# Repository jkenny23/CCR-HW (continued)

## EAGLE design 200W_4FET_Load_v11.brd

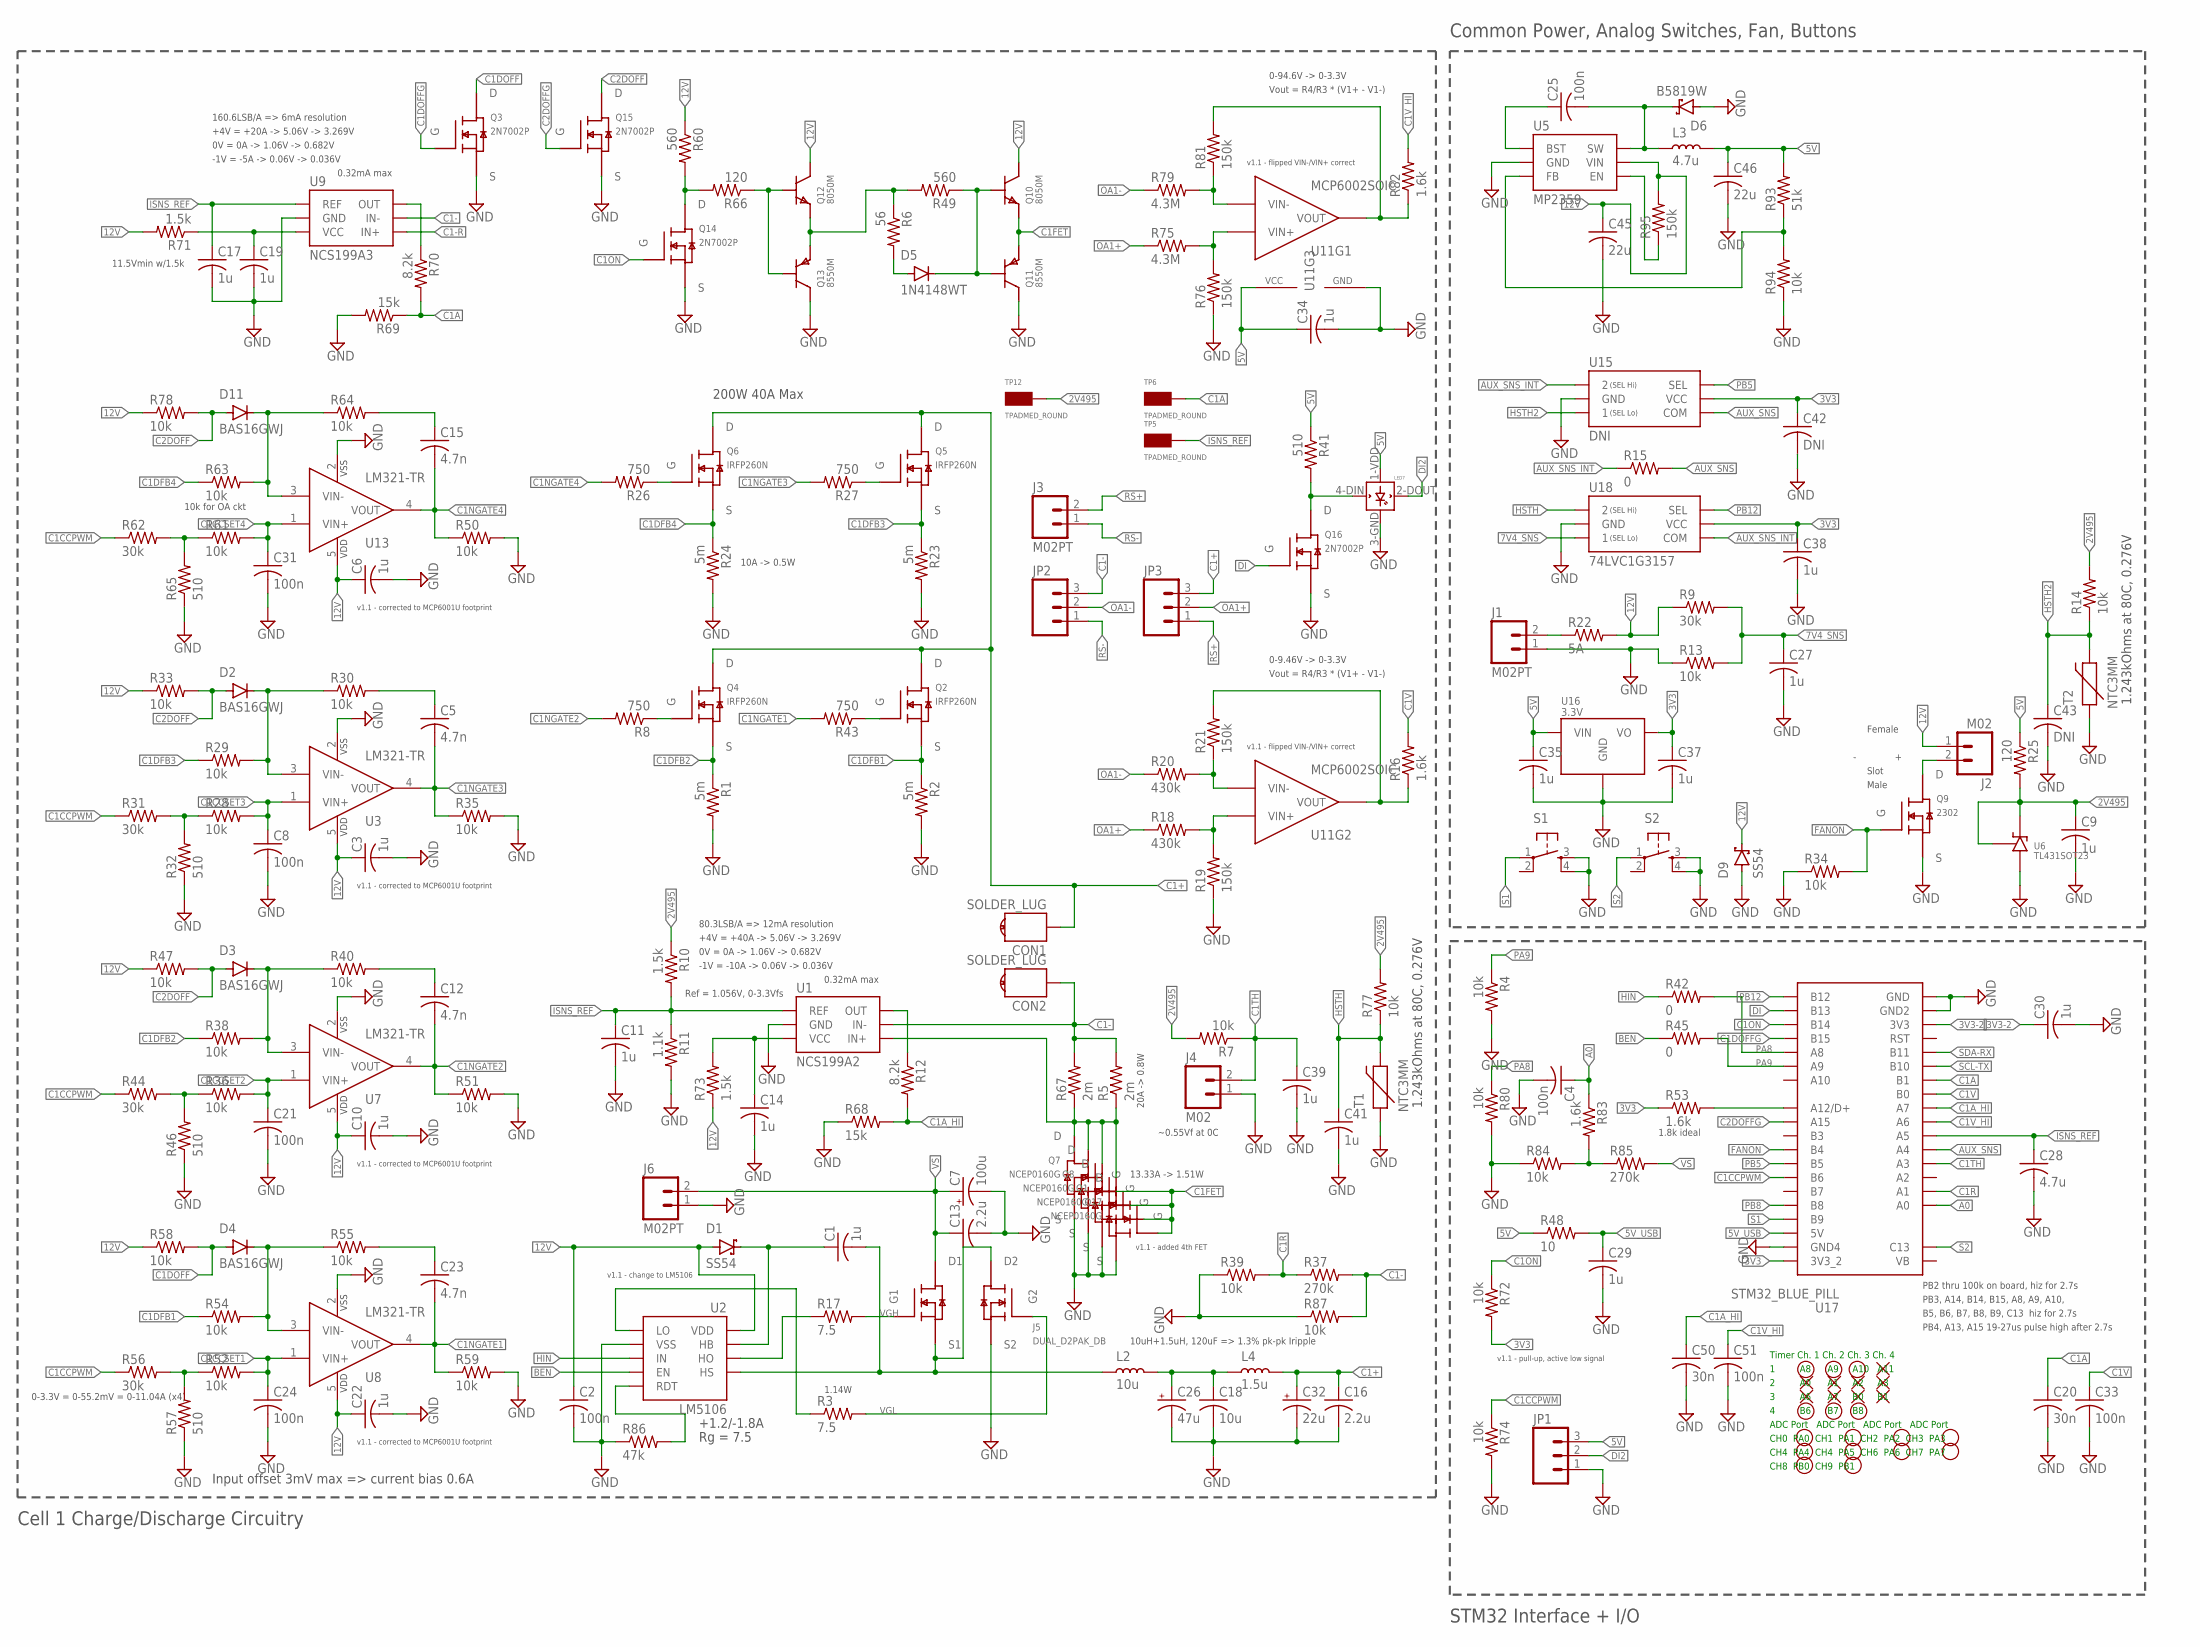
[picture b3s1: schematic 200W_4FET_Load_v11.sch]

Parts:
C1: 1u; C0603
C2: 100n; C0603
C3, C6, C9, C10, C11, C14, C17, C19, C22, C27, C29, C30, C34, C35, C37, C38, C39, C41: 1u; C0402
C4, C8, C21, C24, C25, C31, C33, C51: 100n; C0402
C5, C12, C15, C23: 4.7n; C0402
C7: 100u; E2,5-6E
C13, C16: 2.2u; C1210
C18: 10u; C2220K
C20, C50: 30n; C0402
C26: 47u; E3,5-8
C28: 4.7u; C0402
C32: 22u; E2,5-6E
C42, C43: DNI; C0402
C45: 22u; C0805
C46: 22u; C0603
CON1, CON2: SOLDER_LUG; M4_RA_SOLDTERM
D1, D9: SS54; SMA
D2, D3, D4, D11: BAS16GWJ; SOD323
D5: 1N4148WT; SOD523
D6: B5819W; SOD123W
J1, J3, J6: M02PT; PHOENIXCONTACT1935161
J2, J4: M02; B2B-XH-A
J5: DUAL_D2PAK_DB
JP1, JP2, JP3: M03PTH; 1X03
L2: 10u; INDUCTOR_13.8X12.7
L3: 4.7u; 0805
L4: 1.5u; INDUCTOR_7.4X6.6MM
LED7: WS2812B
Q1, Q7, Q8, Q17: NCEP0160G; DFN5X6-8L
Q2, Q4, Q5, Q6: IRFP260N; TO-247
Q3, Q14, Q15, Q16: 2N7002P; SOT23
Q9: 2302; SOT23
Q10, Q12: 8050M; SOT23
Q11, Q13: 8550M; SOT23
R1, R2, R23, R24: 5m; R1206
R3, R17: 7.5; R2512
R4, R7, R13, R14, R28, R29, R30, R33, R34, R35, R36, R38, R39, R40, R47, R50, R51, R52, R54, R55, R58, R59, R61, R63, R64, R72, R74, R77, R78, R80, R84, R94: 10k; R0402
R5, R67: 2m; R2512
R6: 56; R0402
R8, R26, R27, R43: 750; R0402
R9, R31, R44, R56, R62: 30k; R0402
R10, R71, R73: 1.5k; R0402
R11: 1.1k; R0402
R12, R70: 8.2k; R0402
R15, R42, R45: 0; R0402
R16, R53, R82, R83: 1.6k; R0402
R18, R20: 430k; R0402
R19, R21, R76, R81, R95: 150k; R0402
R22: 5A; R1206
R25, R66: 120; R0402
R32, R41, R46, R57, R65: 510; R0402
R37, R85: 270k; R0402
R48: 10; R0402
R49, R60: 560; R0402
R68, R69: 15k; R0402
R75, R79: 4.3M; R0402
R86: 47k; R0402
R87: 10k; R1206
R93: 51k; R0402
S1, S2: TAC_SWITCHSMD; TACTILE_SWITCH_SMD
T1, T2: NTC3MM; THERMISTOR_3MMX3MM
TP5, TP6, TP12: TPADMED_ROUND; TPAD_MED_ROUND
U1: NCS199A2; SOT-363
U2: LM5106; 10-TSSOP
U3, U7, U8, U13: LM321-TR; SOT23-5
U5: MP2359; SOT23-6
U6: TL431SOT23; SOT23
U9: NCS199A3; SOT-363
U11: MCP6002SOIC; 8-SOIC
U15: DNI; SC70-6
U16: 3.3V; SOT-89
U17: STM32_BLUE_PILL; STM32_BLUE_PILL_USABLE
U18: 74LVC1G3157; SC70-6

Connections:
2V495: C9.1, R7.2, R10.1, R14.2, R25.2, R77.2, TP12.1, U6.1 (K), U6.2 (REF)
3V3: C37.1, C38.1, C42.1, R53.1, R72.2, U15.5 (VCC), U16.1 (VO), U17.3V3_2, U18.5 (VCC)
3V3-2: C30.1, U17.3V3
5V: C34.1, C35.1, C46.1, JP1.3, L3.2, LED7.1-VDD (VDD), R25.1, R41.1, R48.1, R93.2, U11.8 (VCC), U16.3 (VIN)
5V_USB: C29.1, R48.2, U17.5V
7V4_SNS: C27.1, R9.2, R13.2, U18.3 (1)
12V: C2.1, C3.1, C6.1, C10.1, C22.1, C45.1, D1.A (ANODE), D9.K (CATHODE), J2.1, Q10.3 (C), Q12.3 (C), R9.1, R22.2, R33.1, R47.1, R58.1, R60.1, R71.2, R73.1, R78.1, R95.2, U2.1 (VDD), U3.5 (VDD), U5.5 (VIN), U7.5 (VDD), U8.5 (VDD), U13.5 (VDD)
A0: C4.1, R83.1, U17.A0
AUX_SNS: R15.2, U15.4 (COM), U17.A4
AUX_SNS_INT: R15.1, U15.1 (2), U18.4 (COM)
BASE1: Q12.1 (B), Q13.1 (B), R66.1
BASE2: D5.K (CATHODE), Q10.1 (B), Q11.1 (B), R49.1
BEN: R45.1, U2.7 (EN)
C1+: C16.1, C32.+, CON1.P$1, CON1.P$2, CON1.P$3, CON1.P$4, JP3.3, L4.2, Q2.2 (D), Q4.2 (D), Q5.2 (D), Q6.2 (D)
C1-: CON2.P$1, CON2.P$2, CON2.P$3, CON2.P$4, JP2.3, R5.2, R37.2, R67.2, R87.2, U1.5 (IN-), U9.5 (IN-)
C1-R: Q1.EP (D), Q1.EP-TL (D), Q1.EP-TLL (D), Q1.EP-TR (D), Q1.EP-TRR (D), Q7.EP (D), Q7.EP-TL (D), Q7.EP-TLL (D), Q7.EP-TR (D), Q7.EP-TRR (D), Q8.EP (D), Q8.EP-TL (D), Q8.EP-TLL (D), Q8.EP-TR (D), Q8.EP-TRR (D), Q17.EP (D), Q17.EP-TL (D), Q17.EP-TLL (D), Q17.EP-TR (D), Q17.EP-TRR (D), R5.1, R67.1, U1.4 (IN+), U9.4 (IN+)
C1A: C20.1, R69.1, R70.2, TP6.1, U17.B1
C1A_HI: C50.1, R12.2, R68.2, U17.A7
C1CCPWM: R31.1, R44.1, R56.1, R62.1, R74.1, U17.B6
C1CCSET1: C24.1, R52.2, U8.1 (VIN+)
C1CCSET2: C21.1, R36.2, U7.1 (VIN+)
C1CCSET3: C8.1, R28.2, U3.1 (VIN+)
C1CCSET4: C31.1, R61.2, U13.1 (VIN+)
C1DFB1: Q2.3 (S), R2.1, R54.1
C1DFB2: Q4.3 (S), R1.1, R38.1
C1DFB3: Q5.3 (S), R23.1, R29.1
C1DFB4: Q6.3 (S), R24.1, R63.1
C1DOFF: D4.A (ANODE), Q3.3 (D), R58.2
C1DOFFG: Q3.1 (G), U17.B15
C1FET: Q1.4 (G), Q7.4 (G), Q8.4 (G), Q10.2 (E), Q11.2 (E), Q17.4 (G)
C1NGATE1: C23.2, R43.2, R59.1, U8.4 (VOUT)
C1NGATE2: C12.2, R8.2, R51.1, U7.4 (VOUT)
C1NGATE3: C5.2, R27.2, R35.1, U3.4 (VOUT)
C1NGATE4: C15.2, R26.2, R50.1, U13.4 (VOUT)
C1ON: Q14.1 (G), R72.1, U17.B14
C1R: R37.1, R39.2, U17.A1
C1TH: C39.1, J4.2, R7.1, U17.A3
C1V: C33.1, R16.2, U17.B0
C1VFBN: C15.1, R64.2
C1VFBN1: C5.1, R30.2
C1VFBN2: C12.1, R40.2
C1VFBN3: C23.1, R55.2
C1V_HI: C51.1, R82.2, U17.A6
C1V_OA: R16.1, R21.2, U11.7 (VOUT)
C1V_OA1: R81.2, R82.1, U11.1 (VOUT)
C2DOFF: D2.A (ANODE), D3.A (ANODE), D11.A (ANODE), Q15.3 (D), R33.2, R47.2, R78.2
C2DOFFG: Q15.1 (G), U17.A15
DI: Q16.1 (G), U17.B13
DI1: LED7.4-DIN (DIN), Q16.3 (D), R41.2
DI2: JP1.2, LED7.2-DOUT (DOUT)
FANON: Q9.1 (G), R34.2, U17.B4
GND: C2.2, C3.2, C4.2, C6.2, C7.-, C8.2, C9.2, C10.2, C11.2, C13.2, C14.2, C16.2, C17.2, C18.2, C19.2, C20.2, C21.2, C22.2, C24.2, C26.-, C27.2, C28.2, C29.2, C30.2, C31.2, C32.-, C33.2, C34.2, C35.2, C37.2, C38.2, C39.2, C41.2, C42.2, C43.2, C45.2, C46.2, C50.2, C51.2, D6.A (ANODE), D9.A (ANODE), J1.1, J4.1, J5.S2, J6.1, JP1.1, LED7.3-GND (GND), Q1.1 (S), Q1.2 (S), Q1.3 (S), Q3.2 (S), Q7.1 (S), Q7.2 (S), Q7.3 (S), Q8.1 (S), Q8.2 (S), Q8.3 (S), Q9.2 (S), Q11.3 (C), Q13.3 (C), Q14.2 (S), Q15.2 (S), Q16.2 (S), Q17.1 (S), Q17.2 (S), Q17.3 (S), R1.2, R2.2, R4.2, R11.2, R13.1, R19.1, R23.2, R24.2, R32.1, R34.1, R35.2, R39.1, R46.1, R50.2, R51.2, R57.1, R59.2, R65.1, R68.1, R69.2, R74.2, R76.1, R80.2, R84.1, R86.1, R87.1, R94.1, S1.3, S1.4, S2.3, S2.4, T1.1, T2.1, U1.2 (GND), U2.9 (VSS), U3.2 (VSS), U5.2 (GND), U6.3 (A), U7.2 (VSS), U8.2 (VSS), U9.2 (GND), U11.4 (GND), U13.2 (VSS), U15.2 (GND), U16.2 (GND), U16.2@1 (GND), U17.GND, U17.GND2, U17.GND4, U18.2 (GND)
HIN: R42.1, U2.8 (IN)
HO: R17.1, U2.3 (HO)
HSTH: C41.1, R77.1, T1.2, U18.1 (2)
HSTH2: C43.1, R14.1, T2.2, U15.3 (1)
I1SET: R61.1, R62.2, R65.2
I1SET1: R28.1, R31.2, R32.2
I1SET2: R36.1, R44.2, R46.2
I1SET3: R52.1, R56.2, R57.2
IS1O: R12.1, U1.6 (OUT)
ISNS_REF: C11.1, C17.1, C28.1, R10.2, R11.1, TP5.1, U1.1 (REF), U9.1 (REF), U17.A5
LO: R3.1, U2.10 (LO)
unnamed: R75.2, R76.2, U11.3 (VIN+)
unnamed: D2.K (CATHODE), R29.2, R30.1, U3.3 (VIN-)
unnamed: R18.2, R19.2, U11.5 (VIN+)
unnamed: R20.2, R21.1, U11.6 (VIN-)
unnamed: D3.K (CATHODE), R38.2, R40.1, U7.3 (VIN-)
unnamed: D4.K (CATHODE), R54.2, R55.1, U8.3 (VIN-)
unnamed: C18.1, C26.+, L2.2, L4.1
unnamed: C25.1, U5.1 (BST)
unnamed: R79.2, R81.1, U11.2 (VIN-)
unnamed: Q14.3 (D), R60.2, R66.2
unnamed: D5.A (ANODE), R6.2
unnamed: J1.2, R22.1
unnamed: Q12.2 (E), Q13.2 (E), R6.1, R49.2
unnamed: R83.2, R84.2, R85.1
unnamed: R70.1, U9.6 (OUT)
unnamed: R93.1, R94.2, U5.3 (FB)
unnamed: R86.2, U2.6 (RDT)
unnamed: R95.1, U5.4 (EN)
unnamed: D11.K (CATHODE), R63.2, R64.1, U13.3 (VIN-)
unnamed: R53.2, U17.A12 (A12/D+)
unnamed: J2.2, Q9.3 (D)
NCSVCC: C19.1, R71.1, U9.3 (VCC)
NCSVCC2: C14.1, R73.2, U1.3 (VCC)
OA1+: JP3.2, R18.1, R75.1
OA1-: JP2.2, R20.1, R79.1
PA8: R42.2, R80.1, U17.A8
PA9: R4.1, R45.2, U17.A9
PB5: U15.6 (SEL), U17.B5
PB8: U17.B8
PB12: U17.B12, U18.6 (SEL)
Q7G: Q2.1 (G), R43.1
Q7G1: Q4.1 (G), R8.1
Q7G2: Q6.1 (G), R26.1
Q7G3: Q5.1 (G), R27.1
RS+: J3.2, JP3.1
RS-: J3.1, JP2.1
S1: S1.1, U17.B9
S2: S2.1, U17.C13
SCL-TX: U17.B10
SDA-RX: U17.B11
SW5V: C25.2, D6.K (CATHODE), L3.1, U5.6 (SW)
VBST: C1.1, D1.K (CATHODE), U2.2 (HB)
VGH: J5.G1, R17.2
VGL: J5.G2, R3.2
VMID: C1.2, J5.D2, J5.S1, L2.1, U2.4 (HS)
VS: C7.+, C13.1, J5.D1, J6.2, R85.2

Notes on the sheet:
Ref = 1.056V, 0-3.3Vfs
Vout = R4/R3 * (V1+ - V1-)
0-9.46V -> 0-3.3V
~0.55Vf at 0C
STM32 Interface + I/O
0-3.3V = 0-55.2mV = 0-11.04A (x4)
Timer Ch. 1 Ch. 2 Ch. 3 Ch. 4
1 A8 A9 A10 A11
2 A0 A1 A2 A3
3 A6 A7 B0 B1
4 B6 B7 B8
ADC Port ADC Port ADC Port ADC Port
CH0 PA0 CH1 PA1 CH2 PA2 CH3 PA3
CH4 PA4 CH4 PA5 CH6 PA6 CH7 PA7
CH8 PB0 CH9 PB1
Slot
Male
Female
PB2 thru 100k on board, hiz for 2.7s
PB3, A14, B14, B15, A8, A9, A10,
PB4, A13, A15 19-27us pulse high after 2.7s
B5, B6, B7, B8, B9, C13 hiz for 2.7s
1.243kOhms at 80C, 0.276V
Cell 1 Charge/Discharge Circuitry
Common Power, Analog Switches, Fan, Buttons
1.8k ideal
10k for OA ckt
+1.2/-1.8A
Rg = 7.5
1.14W
Input offset 3mV max => current bias 0.6A
10uH+1.5uH, 120uF => 1.3% pk-pk Iripple
200W 40A Max
+4V = +40A -> 5.06V -> 3.269V
-1V = -10A -> 0.06V -> 0.036V
10A -> 0.5W
20A -> 0.8W
13.33A -> 1.51W
0V = 0A -> 1.06V -> 0.682V
80.3LSB/A => 12mA resolution

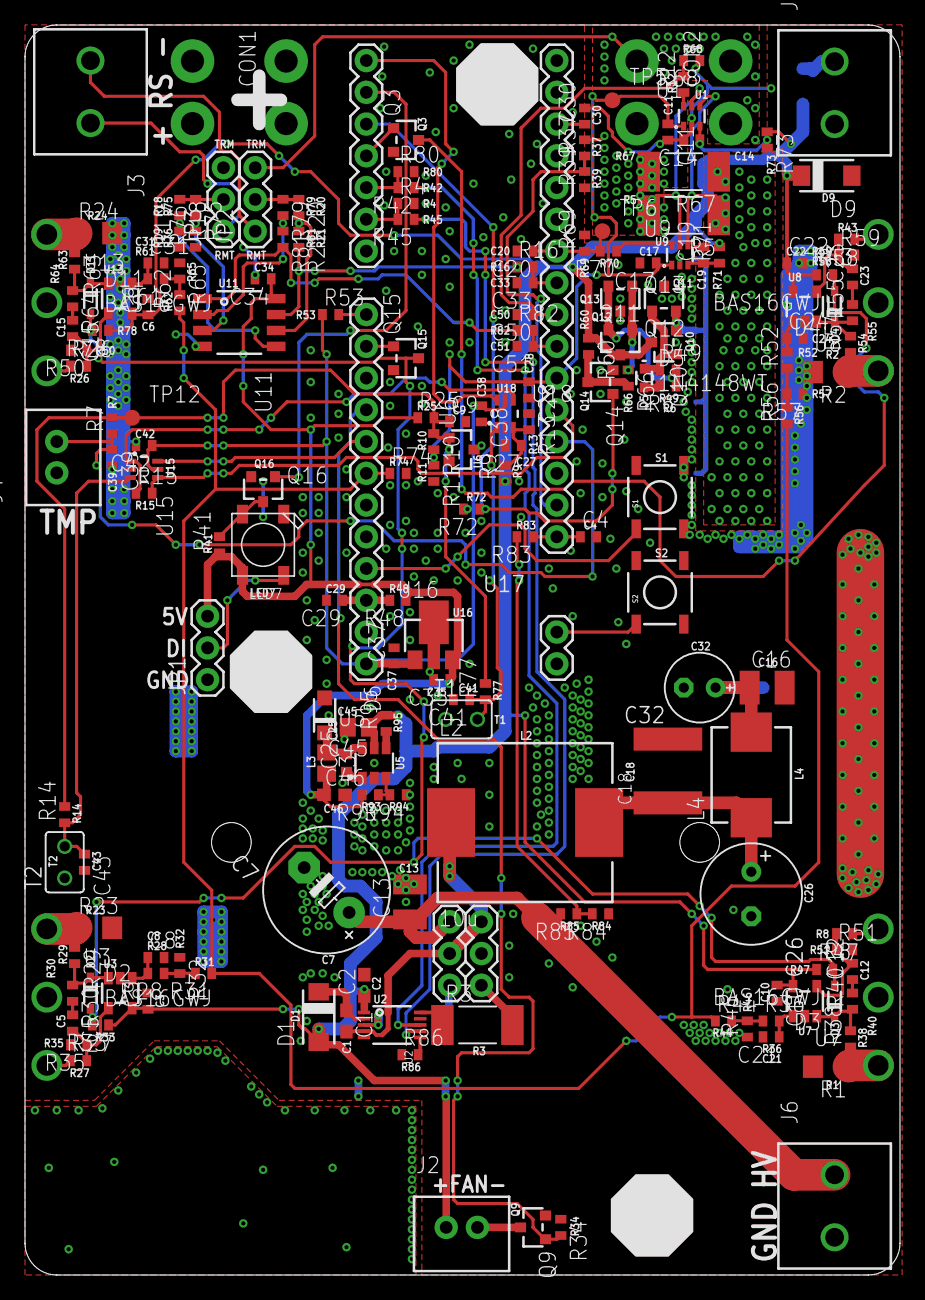
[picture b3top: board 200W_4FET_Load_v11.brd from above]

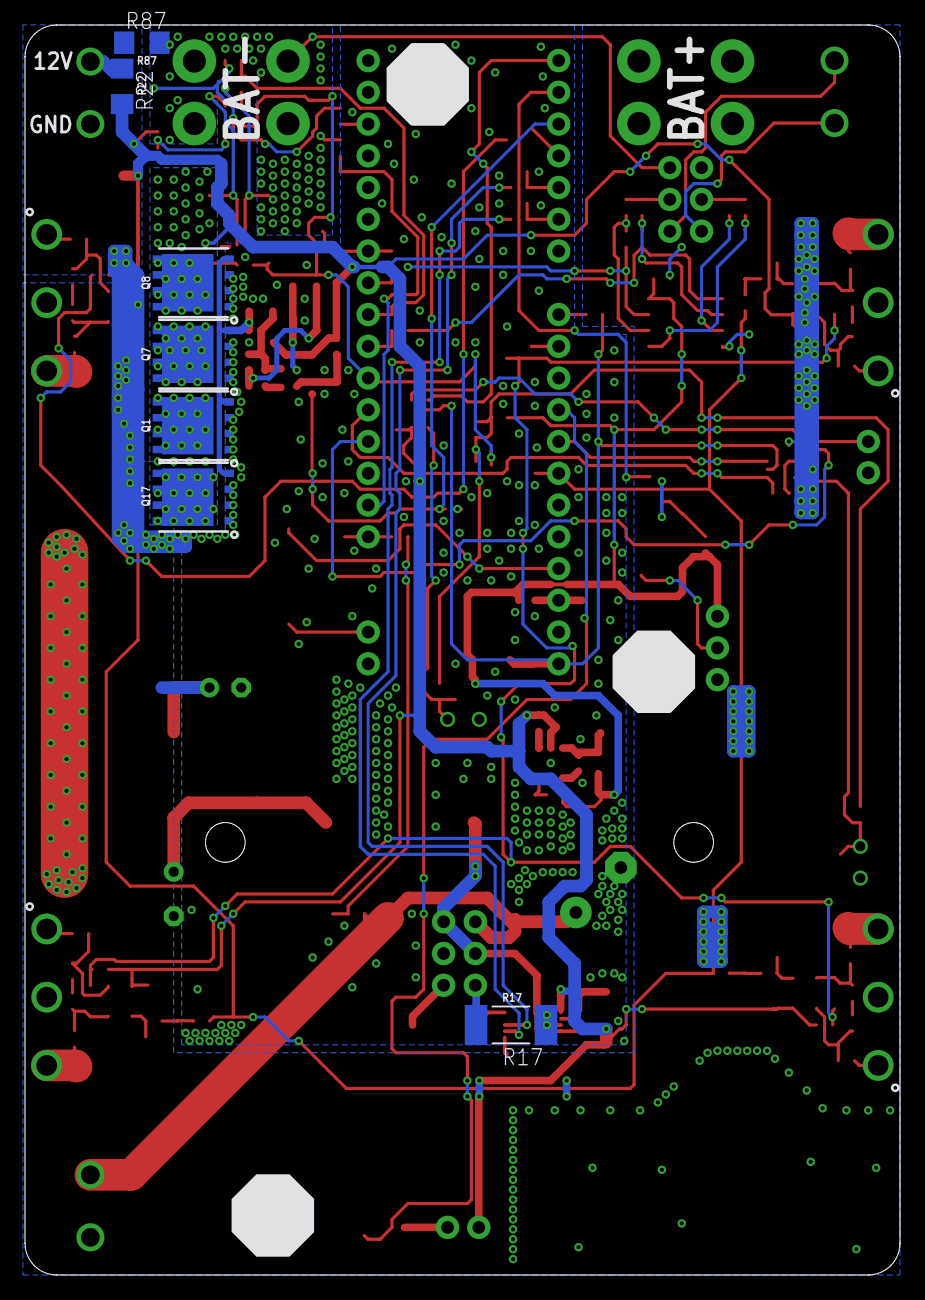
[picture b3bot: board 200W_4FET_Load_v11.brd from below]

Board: 2 copper layers, 70.0 x 100.0 mm, 196 parts (11 on the bottom side), 106 nets.

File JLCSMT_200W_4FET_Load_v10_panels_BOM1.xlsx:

Comment | Designator | Footprint | LCSC Part #（optional）
SW_Tactile | S1, S2 | TAC_SWITCHSMD |  | ext
0 | R15, R42, R45 | 0402_R
1.1k | R11 | 0603_R
1.5k | R10, R71, R73 | 0402_R
1.6k | R16, R53, R82, R83 | 0402_R |  | ext
1N4148WS | D2, D3, D4, D5, D11 | SOD-523
1u 25V | C3, C6, C9, C10, C11, C14, C17, C19, C22, C27, C29, C30, C34, C35, C37, C38, C3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 | 0402_C
2.2u 100V | C13, C16 | 1210_C |  | ext
2N7002 | Q3, Q14, Q15, Q16 | SOT-23
2m | R5, R67 | 2512_R |  | ext
AP1117UR133-B | U16 | SOT-89 |  | ext
4.3M | R75, R79 | 0402_R |  | ext
4.7n | C5, C12, C15, C23 | 0402_C
4.7u | C28 | 0402_C
4.7u | L3 | 0805_L |  | ext
5.6 | R3, R17 | 2512_R |  | ext
5A | R22 | 1206_R |  | ext
5m | R1, R2, R23, R24 | 1206_R |  | ext
8.2k | R12, R70 | 0402_R
10 | R48 | 0402_R
10k | R4, R7, R13, R14, R28, R29, R30, R33, R34, R35, R36, R38, R39, R40, R47, R50, R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 | 0402_R
560n 100V | C1 | 0603_C |  | ext
10u 100V | C18 | 2220_C |  | ext
15k | R68, R69, R94 | 0402_R
22u | C46 | 0603_C
22u | C45 | 0805_C
30k | R9, R31, R44, R56, R62 | 0402_R
30n | C20, C50 | 0402_C |  | ext
56 | R6 | 0603_R
100n | C4, C8, C21, C24, C25, C31, C33, C51 | 0402_C
100n | C2 | 0603_C
110k | R93, R95 | 0603_R
120 | R25, R66 | 0402_R
150k | R19, R21, R76, R81 | 0402_R
270k | R37, R85 | 0603_R
430k | R18, R20 | 0603_R
510 | R32, R41, R46, R57, R65 | 0402_R
560 | R49, R60 | 0603_R
750 | R8, R26, R27, R43 | 0603_R
2302 | Q9 | SOT-23 |  | ext
8050M | Q10, Q12 | SOT-23 |  | ext
8550M | Q11, Q13 | SOT-23 |  | ext
SN74LVC1G3157 | U15, U18 | SC-70-6 |  | ext
FD2203S | U2 | SOIC-8 |  | ext
JW5052C | U5 | SOT-23-6 |  | ext
LM321-TR | U3, U7, U8, U13 | SOT-23-5 |  | ext
MCP6002 | U11 | SOIC-8
NCEP0160G | Q1, Q7, Q8 | DFN5X6-8L |  | ext
SS54 | D9 | SMA
SS210 | D1 | SMA
CJ431 | U6 | SOT-23
WS2812B | LED7 | WS2812B |  | ext

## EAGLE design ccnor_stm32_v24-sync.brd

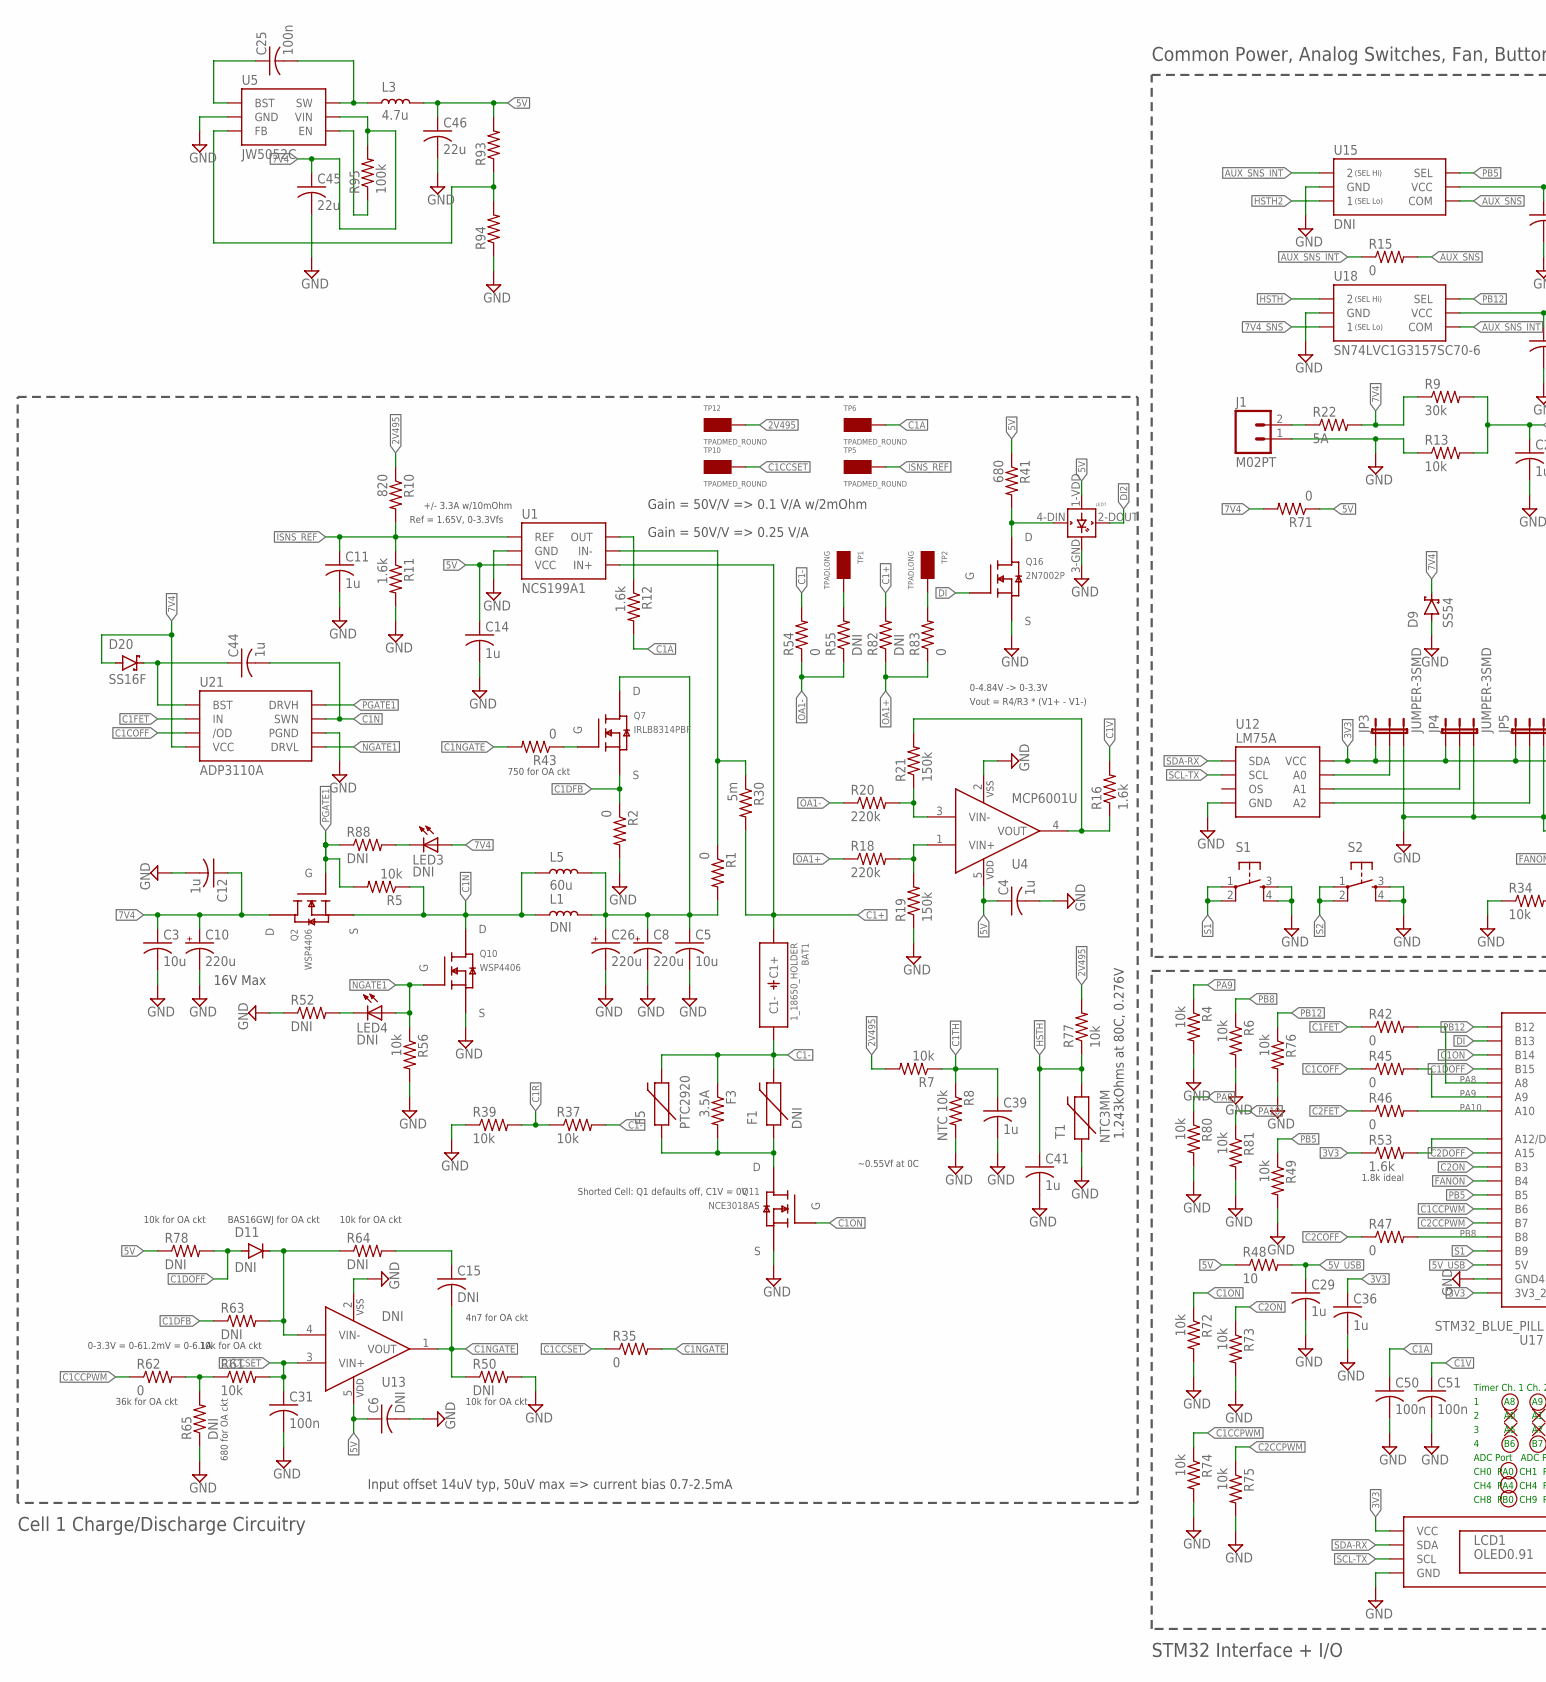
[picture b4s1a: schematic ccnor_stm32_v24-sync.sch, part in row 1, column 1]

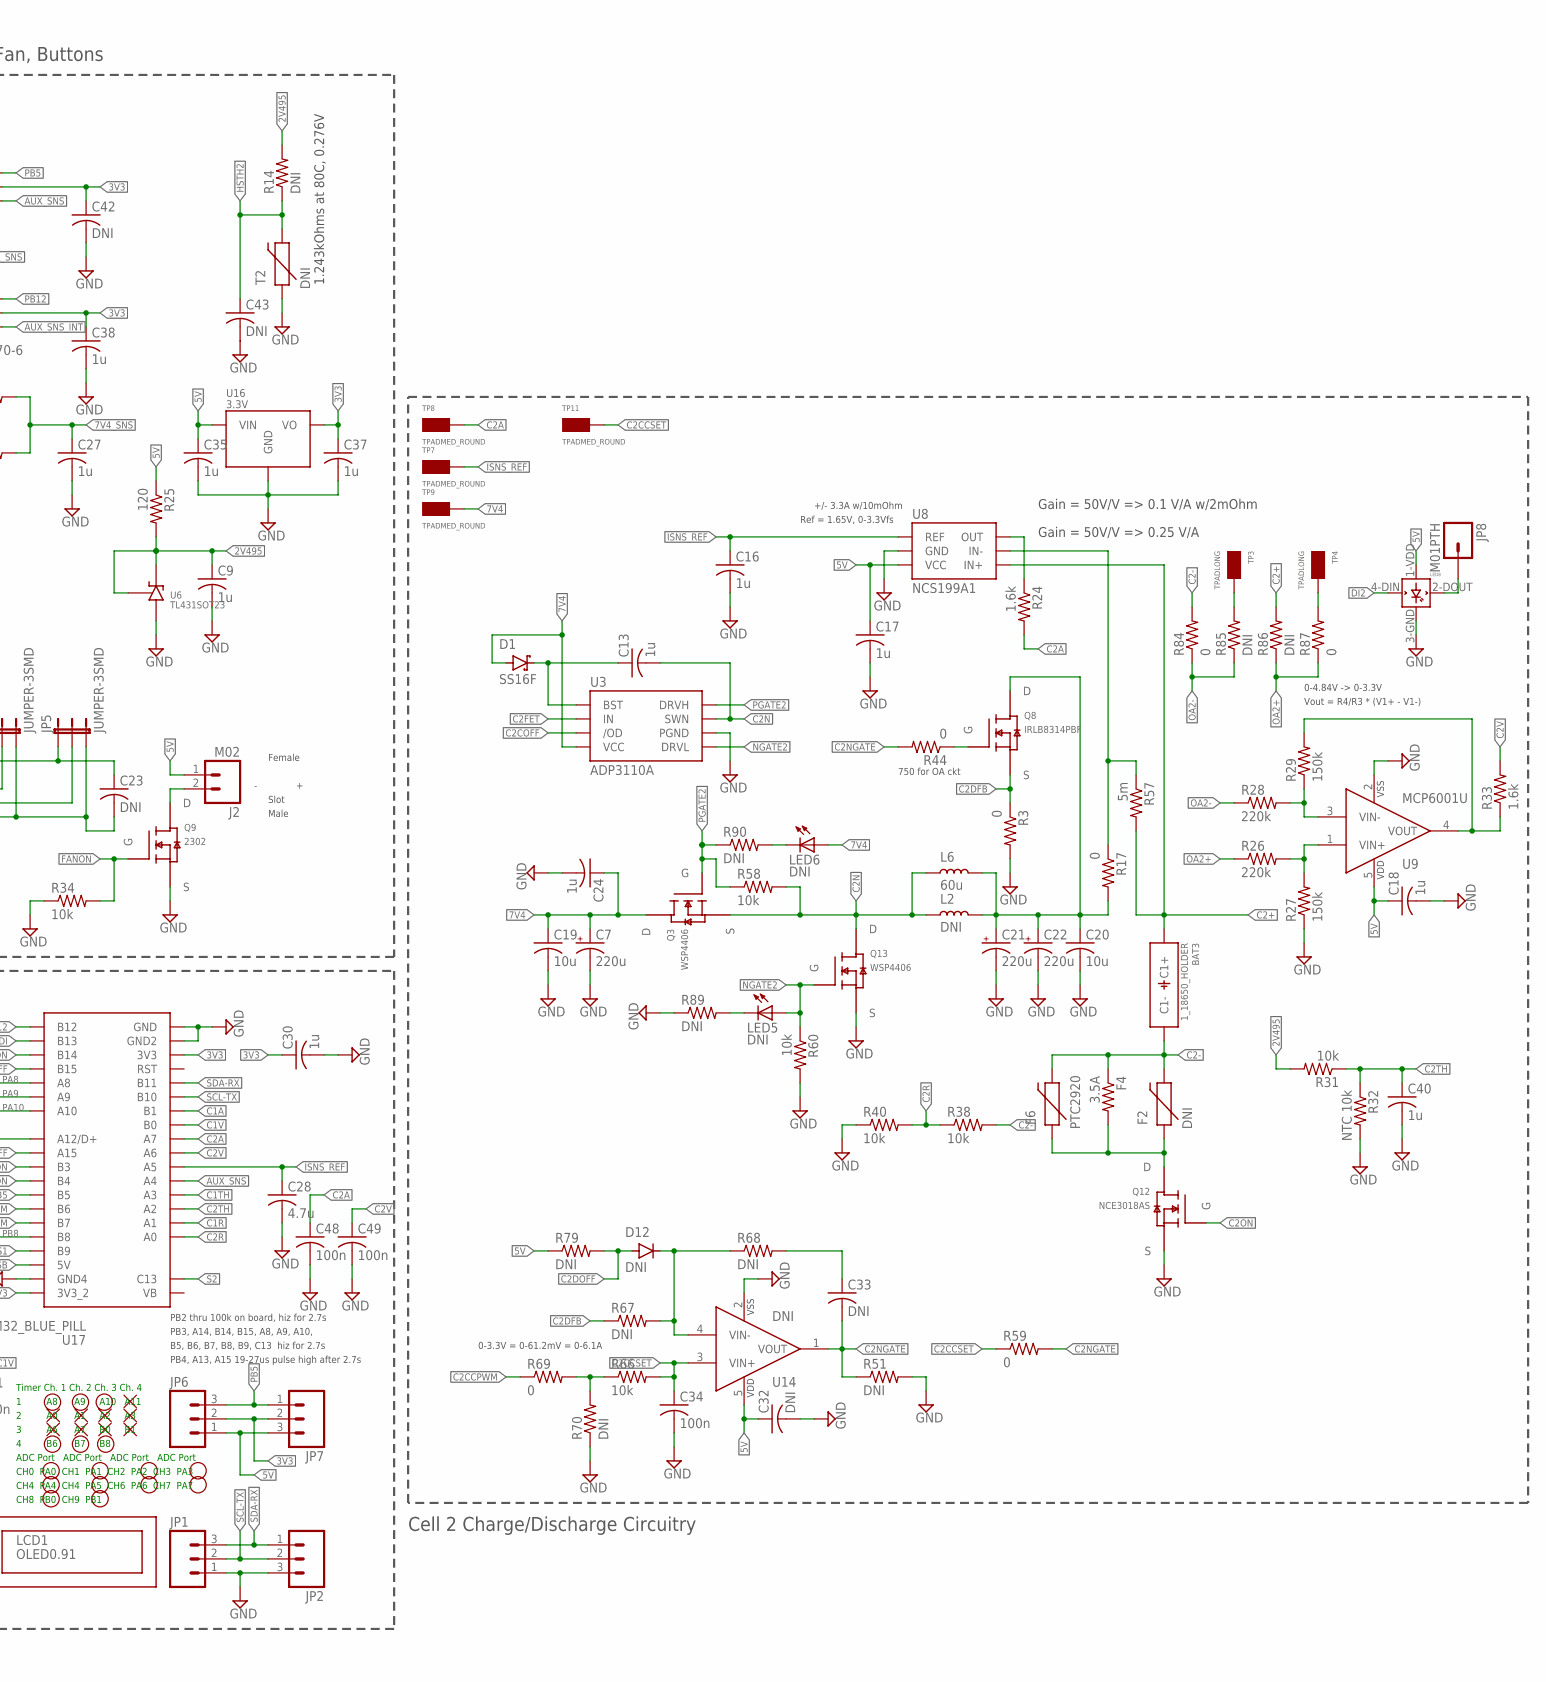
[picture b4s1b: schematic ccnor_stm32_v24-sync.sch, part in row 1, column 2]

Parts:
BAT1, BAT3: 1_18650_HOLDER; 1S_18650_SMD_NH
C3, C5, C19, C20: 10u; C1206
C4, C9, C11, C12, C14, C16, C17, C18, C24, C27, C29, C30, C35, C36, C37, C38, C39, C40, C41: 1u; C0402
C6, C15, C23, C32, C33, C42, C43: DNI; C0402
C7, C8, C10, C21, C22, C26: 220u; PANASONIC_D
C13, C44: 1u; C0603
C25, C31, C34, C48, C49, C50, C51: 100n; C0402
C28: 4.7u; C0402
C45: 22u; C0805
C46: 22u; C0603
D1, D20: SS16F; SOD123
D9: SS54; SMA
D11, D12: DNI; SOD323
F1, F2: DNI; 1812
F3, F4: 3.5A; R1206
F5, F6: PTC2920; 2920
J1: M02PT; PHOENIXCONTACT1935161
J2: M02; B2B-XH-A
JP1, JP2, JP6, JP7: M03PTH; 1X03
JP3, JP4, JP5: JUMPER-3SMD; SJ_3
JP8: M01PTH; 1X01
L1, L2: DNI; INDUCTOR_SMD_13MM
L3: 4.7u; 0805
L5, L6: 60u; INDUCTOR_10A_8.2MMX21MM
LCD1: OLED0.91
LED3, LED4, LED5, LED6: DNI; CHIPLED_0603
LED7, LED8: WS2812B
Q2, Q3, Q10, Q13: WSP4406; 8-SOIC
Q7, Q8: IRLB8314PBF; TO-220
Q9: 2302; SOT23
Q11, Q12: NCE3018AS; 8-SOIC
Q16: 2N7002P; SOT23
R1, R2, R3, R17: 0; R1206
R4, R5, R6, R7, R13, R31, R34, R37, R38, R39, R40, R49, R56, R58, R60, R61, R66, R72, R73, R74, R75, R76, R77, R80, R81: 10k; R0402
R8, R32: NTC 10k; R0402
R9: 30k; R0402
R10: 820; R0402
R11, R12, R16, R24, R33, R53: 1.6k; R0402
R14, R50, R51, R52, R55, R63, R64, R65, R67, R68, R70, R78, R79, R82, R85, R86, R88, R89, R90: DNI; R0402
R15, R35, R42, R43, R44, R45, R46, R47, R54, R59, R62, R69, R83, R84, R87: 0; R0402
R18, R20, R26, R28: 220k; R0402
R19, R21, R27, R29: 150k; R0402
R22: 5A; R1206
R25: 120; R0402
R30, R57: 5m; R1206
R41: 680; R0402
R48: 10; R0402
R71: 0; R0603
R93, R94: R-US_R0402; R0402
R95: 100k; R0402
S1, S2: TAC_SWITCHSMD; TACTILE_SWITCH_SMD
T1: NTC3MM; THERMISTOR_3MMX3MM
T2: DNI; THERMISTOR_3MMX3MM
TP1, TP2, TP3, TP4: TPADLONG; TPAD_LONG
TP5, TP6, TP7, TP8, TP9, TP10, TP11, TP12: TPADMED_ROUND; TPAD_MED_ROUND
U1, U8: NCS199A1; SOT-363
U3, U21: ADP3110A; 8-SOIC
U4, U9: MCP6001U; SOT23-5
U5: JW5052C; SOT23-6
U6: TL431SOT23; SOT23
U12: LM75A; 8-SOIC
U13, U14: DNI; SOT23-5
U15: DNI; SC70-6
U16: 3.3V; SOT-89
U17: STM32_BLUE_PILL; STM32_BLUE_PILL_USABLE
U18: SN74LVC1G3157SC70-6; SC70-6

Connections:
2V495: C9.1, R7.2, R10.1, R14.2, R25.2, R31.2, R77.2, TP12.1, U6.1 (K), U6.2 (REF)
3V3: C23.1, C30.1, C36.1, C37.1, C38.1, C42.1, JP3.1, JP4.1, JP5.1, JP6.2, JP7.2, LCD1.2-VCC (VCC), R53.1, U12.8 (VCC), U15.5 (VCC), U16.1 (VO), U17.3V3, U17.3V3_2, U18.5 (VCC)
5V: C4.1, C6.1, C14.1, C17.1, C18.1, C32.1, C35.1, C46.1, J2.1, JP6.1, JP7.3, L3.2, LED7.1-VDD (VDD), LED8.1-VDD (VDD), R25.1, R41.1, R48.1, R71.1, R78.1, R79.1, R93.2, U1.3 (VCC), U4.5 (VDD), U8.3 (VCC), U9.5 (VDD), U13.5 (VDD), U14.5 (VDD), U16.3 (VIN)
5V_USB: C29.1, R48.2, U17.5V
7V4: C3.1, C7.+, C10.+, C12.1, C19.1, C24.1, C45.1, D1.A (ANODE), D9.K (CATHODE), D20.A (ANODE), LED3.A, LED6.A, Q2.5 (D), Q2.6 (D), Q2.7 (D), Q2.8 (D), Q3.5 (D), Q3.6 (D), Q3.7 (D), Q3.8 (D), R9.1, R22.2, R71.2, R95.2, TP9.1, U3.4 (VCC), U5.5 (VIN), U21.4 (VCC)
7V4_SNS: C27.1, R9.2, R13.2, U18.3 (1)
AUX_SNS: R15.2, U15.4 (COM), U17.A4
AUX_SNS_INT: R15.1, U15.1 (2), U18.4 (COM)
BST: C44.1, D20.K (CATHODE), U21.1 (BST)
BST2: C13.1, D1.K (CATHODE), U3.1 (BST)
C1+: BAT1.1+ (C1+), R30.2, R82.2, U1.4 (IN+)
C1-: BAT1.1- (C1-), F1.2, F3.1, F5.K (2), R37.2, R54.2
C1A: C50.1, R12.2, TP6.1, U17.B1
C1CCPWM: R62.1, R74.1, U17.B6
C1CCSET: C31.1, R35.1, R61.2, TP10.1, U13.3 (VIN+)
C1COFF: R45.1, U21.3 (/OD)
C1DFB: Q7.3 (S), R2.1, R63.1
C1DOFF: D11.A (ANODE), R78.2, U17.B15
C1FET: R42.1, U21.2 (IN)
C1N: C44.2, L1.1, L5.P$1, Q2.1 (S), Q2.2 (S), Q2.3 (S), Q10.5 (D), Q10.6 (D), Q10.7 (D), Q10.8 (D), R5.1, U21.7 (SWN)
C1NGATE: C15.2, R35.2, R43.2, R50.1, U13.1 (VOUT)
C1ON: Q11.4 (G), R72.1, U17.B14
C1R: R37.1, R39.2, U17.A1
C1TH: C39.1, R7.1, R8.1, U17.A3
C1V: C51.1, R16.2, U17.B0
C1VFBN: C15.1, R64.2
C1VFBN2: C33.1, R68.2
C1V_OA: R16.1, R21.2, U4.4 (VOUT)
C2+: BAT3.1+ (C1+), R57.2, R86.2, U8.4 (IN+)
C2-: BAT3.1- (C1-), F2.2, F4.1, F6.K (2), R38.2, R84.2
C2A: C48.1, R24.2, TP8.1, U17.A7
C2CCPWM: R69.1, R75.1, U17.B7
C2CCSET: C34.1, R59.1, R66.2, TP11.1, U14.3 (VIN+)
C2COFF: R47.1, U3.3 (/OD)
C2DFB: Q8.3 (S), R3.1, R67.1
C2DOFF: D12.A (ANODE), R79.2, U17.A15
C2FET: R46.1, U3.2 (IN)
C2N: C13.2, L2.1, L6.P$1, Q3.1 (S), Q3.2 (S), Q3.3 (S), Q13.5 (D), Q13.6 (D), Q13.7 (D), Q13.8 (D), R58.2, U3.7 (SWN)
C2NGATE: C33.2, R44.2, R51.1, R59.2, U14.1 (VOUT)
C2ON: Q12.4 (G), R73.1, U17.B3
C2R: R38.1, R40.2, U17.A0
C2TH: C40.1, R31.1, R32.1, U17.A2
C2V: C49.1, R33.2, U17.A6
C2V_OA: R29.2, R33.1, U9.4 (VOUT)
DI: Q16.1 (G), U17.B13
DI1: LED7.4-DIN (DIN), Q16.3 (D), R41.2
DI2: LED7.2-DOUT (DOUT), LED8.4-DIN (DIN)
FANON: Q9.1 (G), R34.2, U17.B4
GND: C3.2, C4.2, C5.2, C6.2, C7.-, C8.-, C9.2, C10.-, C11.2, C12.2, C14.2, C16.2, C17.2, C18.2, C19.2, C20.2, C21.-, C22.-, C23.2, C24.2, C26.-, C27.2, C28.2, C29.2, C30.2, C31.2, C32.2, C34.2, C35.2, C36.2, C37.2, C38.2, C39.2, C40.2, C41.2, C42.2, C43.2, C45.2, C46.2, C48.2, C49.2, C50.2, C51.2, D9.A (ANODE), J1.1, JP1.1, JP2.3, JP3.3, JP4.3, JP5.3, LCD1.1=GND (GND), LED7.3-GND (GND), LED8.3-GND (GND), Q9.2 (S), Q10.1 (S), Q10.2 (S), Q10.3 (S), Q11.1 (S), Q11.2 (S), Q11.3 (S), Q12.1 (S), Q12.2 (S), Q12.3 (S), Q13.1 (S), Q13.2 (S), Q13.3 (S), Q16.2 (S), R2.2, R3.2, R4.2, R6.2, R8.2, R11.2, R13.1, R19.1, R27.1, R32.2, R34.1, R39.1, R40.1, R49.2, R50.2, R51.2, R52.1, R56.2, R60.2, R65.1, R70.1, R72.2, R73.2, R74.2, R75.2, R76.2, R80.2, R81.2, R89.1, R94.1, S1.3, S1.4, S2.3, S2.4, T1.1, T2.1, U1.2 (GND), U3.6 (PGND), U4.2 (VSS), U5.2 (GND), U6.3 (A), U8.2 (GND), U9.2 (VSS), U12.4 (GND), U13.2 (VSS), U14.2 (VSS), U15.2 (GND), U16.2 (GND), U16.2@1 (GND), U17.GND, U17.GND2, U17.GND4, U18.2 (GND), U21.6 (PGND)
HSTH: C41.1, R77.1, T1.2, U18.1 (2)
HSTH2: C43.1, R14.1, T2.2, U15.3 (1)
I1SET: R61.1, R62.2, R65.2
I1SET2: R66.1, R69.2, R70.2
IN-1: R1.1, R30.1, U1.5 (IN-)
IN-2: R17.1, R57.1, U8.5 (IN-)
IS1O: R12.1, U1.6 (OUT)
IS1O1: R24.1, U8.6 (OUT)
ISNS_REF: C11.1, C16.1, C28.1, R10.2, R11.1, TP5.1, TP7.1, U1.1 (REF), U8.1 (REF), U17.A5
unnamed: LED3.C, R88.2
unnamed: F2.1, F4.2, F6.A (1), Q12.5 (D), Q12.6 (D), Q12.7 (D), Q12.8 (D)
unnamed: R18.2, R19.2, U4.1 (VIN+)
unnamed: R20.2, R21.1, U4.3 (VIN-)
unnamed: R85.2, TP3.P$1
unnamed: JP8.1, LED8.2-DOUT (DOUT)
unnamed: D12.K (CATHODE), R67.2, R68.1, U14.4 (VIN-)
unnamed: C25.1, U5.1 (BST)
unnamed: LED6.C, R90.2
unnamed: C25.2, L3.1, U5.6 (SW)
unnamed: J1.2, R22.1
unnamed: R26.2, R27.2, U9.1 (VIN+)
unnamed: R28.2, R29.1, U9.3 (VIN-)
unnamed: R93.1, R94.2, U5.3 (FB)
unnamed: R55.2, TP1.P$1
unnamed: LED4.C, R52.2
unnamed: R95.1, U5.4 (EN)
unnamed: D11.K (CATHODE), R63.2, R64.1, U13.4 (VIN-)
unnamed: LED5.C, R89.2
unnamed: R53.2, U17.A12 (A12/D+)
unnamed: JP3.2, U12.7 (A0)
unnamed: JP4.2, U12.6 (A1)
unnamed: JP5.2, U12.5 (A2)
unnamed: R83.2, TP2.P$1
unnamed: R87.2, TP4.P$1
unnamed: F1.1, F3.2, F5.A (1), Q11.5 (D), Q11.6 (D), Q11.7 (D), Q11.8 (D)
unnamed: J2.2, Q9.3 (D)
NGATE1: LED4.A, Q10.4 (G), R56.1, U21.5 (DRVL)
NGATE2: LED5.A, Q13.4 (G), R60.1, U3.5 (DRVL)
OA1+: R18.1, R82.1, R83.1
OA1-: R20.1, R54.1, R55.1
OA2+: R26.1, R86.1, R87.1
OA2-: R28.1, R84.1, R85.1
PA8: R42.2, R80.1, U17.A8
PA9: R4.1, R45.2, U17.A9
PA10: R46.2, R81.1, U17.A10
PB5: JP6.3, JP7.1, R49.1, U15.6 (SEL), U17.B5
PB8: R6.1, R47.2, U17.B8
PB12: R76.1, U17.B12, U18.6 (SEL)
PGATE1: Q2.4 (G), R5.2, R88.1, U21.8 (DRVH)
PGATE2: Q3.4 (G), R58.1, R90.1, U3.8 (DRVH)
PWR1: C5.1, C8.+, C26.+, L1.2, L5.P$2, Q7.2 (D), R1.2
PWR2: C20.1, C21.+, C22.+, L2.2, L6.P$2, Q8.2 (D), R17.2
Q7G: Q7.1 (G), R43.1
Q8G: Q8.1 (G), R44.1
S1: S1.1, S1.2, U17.B9
S2: S2.1, S2.2, U17.C13
SCL-TX: JP1.2, JP2.2, LCD1.3=SCL (SCL), U12.2 (SCL), U17.B10
SDA-RX: JP1.3, JP2.1, LCD1.4-SDA (SDA), U12.1 (SDA), U17.B11

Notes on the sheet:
Gain = 50V/V => 0.25 V/A
Ref = 1.65V, 0-3.3Vfs
Gain = 50V/V => 0.1 V/A w/2mOhm
+/- 3.3A w/10mOhm
Vout = R4/R3 * (V1+ - V1-)
0-4.84V -> 0-3.3V
Shorted Cell: Q1 defaults off, C1V = 0V
~0.55Vf at 0C
16V Max
STM32 Interface + I/O
0-3.3V = 0-61.2mV = 0-6.1A
Input offset 14uV typ, 50uV max => current bias 0.7-2.5mA
Timer Ch. 1 Ch. 2 Ch. 3 Ch. 4
1 A8 A9 A10 A11
2 A0 A1 A2 A3
3 A6 A7 B0 B1
4 B6 B7 B8
ADC Port ADC Port ADC Port ADC Port
CH0 PA0 CH1 PA1 CH2 PA2 CH3 PA3
CH4 PA4 CH4 PA5 CH6 PA6 CH7 PA7
CH8 PB0 CH9 PB1
Slot
Male
Female
PB2 thru 100k on board, hiz for 2.7s
PB3, A14, B14, B15, A8, A9, A10,
PB4, A13, A15 19-27us pulse high after 2.7s
B5, B6, B7, B8, B9, C13 hiz for 2.7s
1.243kOhms at 80C, 0.276V
Cell 1 Charge/Discharge Circuitry
Cell 2 Charge/Discharge Circuitry
Common Power, Analog Switches, Fan, Buttons
1.8k ideal
750 for OA ckt
36k for OA ckt
680 for OA ckt
10k for OA ckt
BAS16GWJ for OA ckt
4n7 for OA ckt
